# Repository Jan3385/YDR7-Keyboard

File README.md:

# YDR7-Keyboard

A mechanical keyboard build on YD-RP2040 with an OLED display and backlights

Build for **MX** switches

A sligthly modified 96% keyboard layout with 4 extra keys for managing onboard firmware (103 keys total)

## Why is this one special

It's a keyboard with a customisable OLED that helps to manage, and control parts of the firmware like changing backlighting color, showing typing speed and much more

The firmware is also open-source so anyone can customise and add features to their keyboard

## PCB

The keyboard uses a custom PCB with the YD-RP2040 attached to it providing a USB-C connection along with power to the board

The YD-RP2040 is the devboard with a chip running this project. You may be able to use a standard Raspberry PI pico but that was not tested

## Case

The keyboard is comprised out of 3 parts. The panel which holds the switches, a back panel and a front panel

Due to their size its impossible to print an entire piece at once, thats why there are sliced versions in the `CAD/Sliced` folder. You can print them separately and then weld them with a soldering iron together. You should weld the front and the back piece but not the panels as they are held together by the frame anyway

> [!WARNING]
> Due to the size of the keyboard, even the sliced version requires 216 x 139 mm or larger printing plate

## Compiling & flashing firmware

> [!NOTE]
> You should have CMAKE and GCC installed along with Arm embedded GNU Toolchain `arm-none-eabi-gcc`

For compilation run the following commands in the project folder:
Note that the first command may take a while as it is downloading the SDK from git

> cmake -S Firmware -B Firmware/build -G "Ninja"

> cmake --build Firmware/build --target Keyboard_Firmware

To load the firmware into the RP2040 chip, press the **BOOT** button on the YD-RP2040 devboard and plug it into your computer. It should appear as a drive in which you insert the `Keyboard_Firmware.uf2` file inside the `Firmware/build/` folder. The keyboard should reboot itself and load the active firmware

To reflash the board just repeat the steps above

## BOM

| Product name | Product description | Product link | Product unit cost inc. Tax (€) | Product amount | Product total cost (€) | Running total (€ with tax and shipping) |
|---------------|---------------------|---------------|----------------------------------|----------------|------------------------|------------------------------------------|
| YD-RP2040 | RPI pico-like microcontroller board | [Link](https://www.aliexpress.com/item/1005006152339711.html) | 2.99 € | 1 | 2.99 € | 2.99 € |
| 74AHCT125DR | Logic level shifter IO | [Link](https://www.aliexpress.com/item/1005010022053816.html) | 3.01 € | 1 | 3.01 € | 6.00 € |
| 100nF 0805 Ceramic Capacitor (>= 6.3V) | Decoupling capacitor | [Link](https://www.aliexpress.com/item/1005007470747384.html) | 0.02 € | 105 | 1.82 € | 7.82 € |
| 10kΩ 0805 Resistor | Pull-up resistor | [Link](https://www.aliexpress.com/item/1005009805187579.html) | 0.02 € | 2 | 0.04 € | 7.85 € |
| 1N4148W Diode | Keyboard matrix diode | [Link](https://www.aliexpress.com/item/4000685043735.html) | 0.02 € | 103 | 1.77 € | 9.63 € |
| Kailh Hot-Swap Sockets for Gateron x103 | PCB sockets for switches | [Link](https://www.aliexpress.com/item/1005009594313632.html) | 8.24 € | 1 | 8.24 € | 17.87 € |
| Gateron Switch G Pro 3.0 | Mechanical keyboard switches | [Link](https://kurokeeb.com/products/gateron-switch-g-pro-3-0) | 0.37 € | 103 | 38.11 € | 55.98 € |
| 1.5 Inch OLED Display 128x128 I2C | OLED Screen | [Link](https://www.aliexpress.com/item/1005009409829497.html) | 4.25 € | 1 | 4.25 € | 60.23 € |
| SK6812 Mini RGB LED x200 | Backlight LEDs | [Link](https://www.aliexpress.com/item/1005007696173500.html) | 3.38 € | 2 | 6.76 € | 66.99 € |
| Keycap set | set of keycaps for keyboard | [Link](https://www.aliexpress.com/item/1005007996240625.html) | 16.93 € | 1 | 16.93 € | 83.92 € |
| M3x8 screws | screws for PCB and case assembly | [Link](https://www.aliexpress.com/item/1005008585550992.html) | 0.05 € | 8 | 0.40 € | 84.32 € |
| Hot melt inserts MxL4xOD4.2 | inserts for case assembly | [Link](https://www.aliexpress.com/item/1005006071488810.html) | 0.11 € | 8 | 0.88 € | 85.20 € |
| Silicone feet 12x3mm x4 | anti-slip feet for case | [Link](https://www.aliexpress.com/item/1005006954839245.html) | 0.72 € | 1 | 0.72 € | 85.92 € |
| PCB | w/o assembly (estimate) | [Link](https://www.jlcpcb.com/) | 40.00 € | 1 | 40.00 € | 125.92 € |

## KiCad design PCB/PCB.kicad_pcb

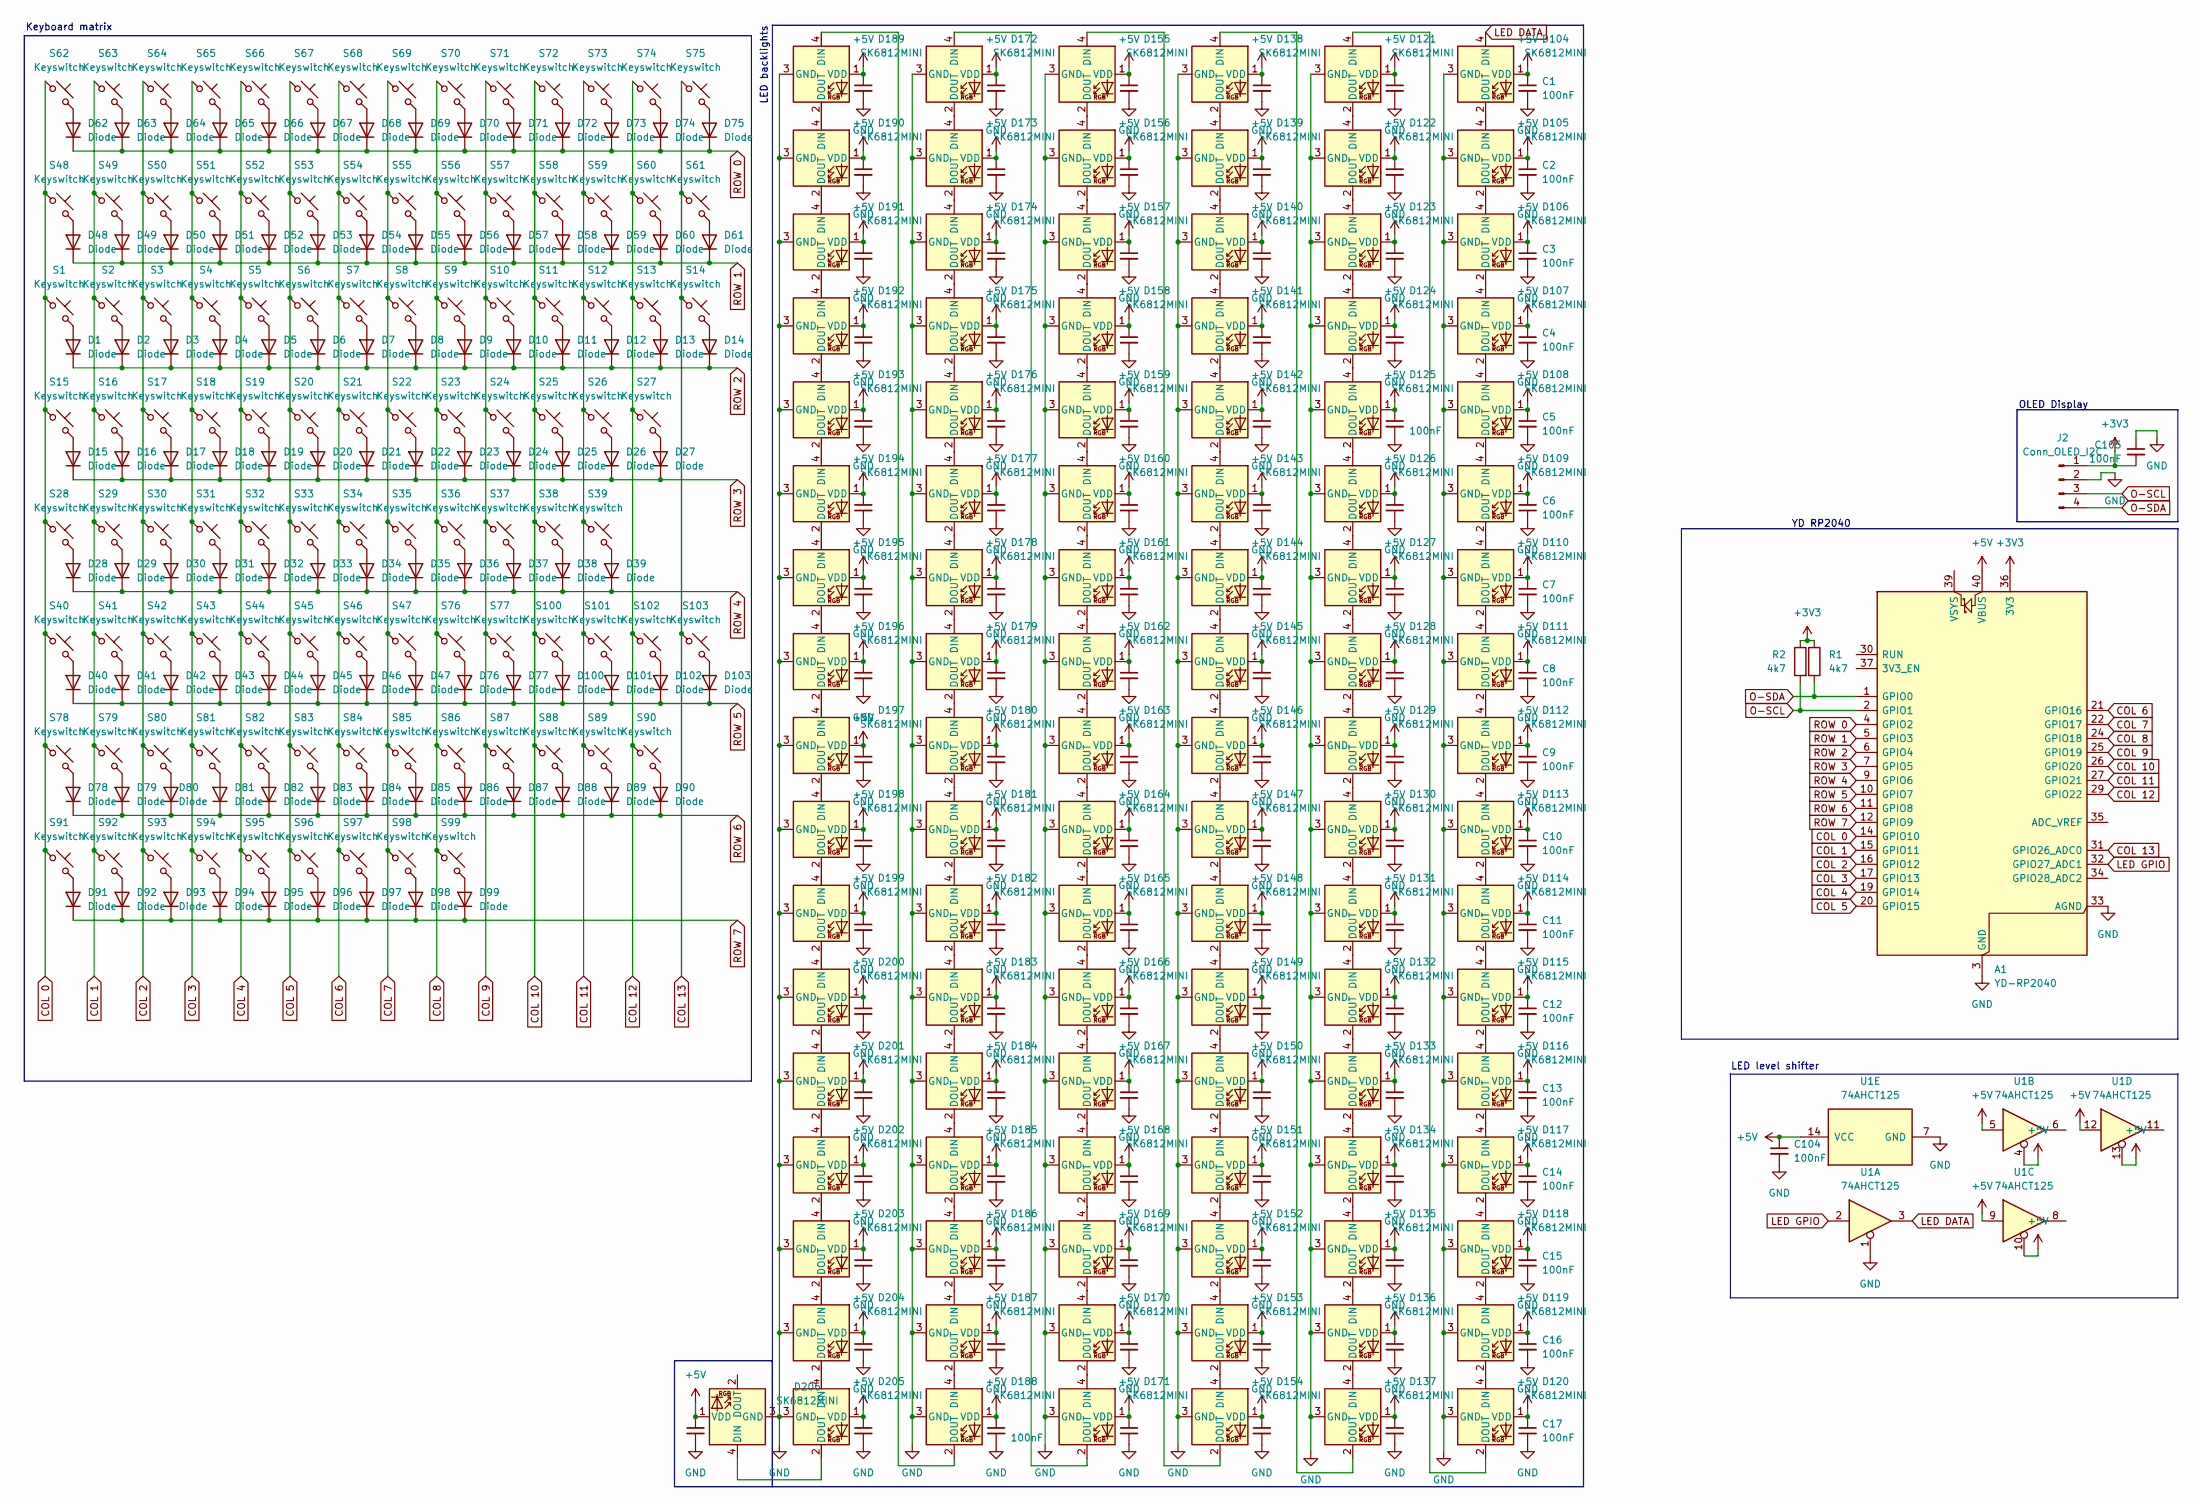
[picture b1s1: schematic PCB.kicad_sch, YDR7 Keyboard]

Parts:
A1: YD-RP2040; RaspberryPi_Pico_SMD_HandSolder
C1, C2, C3, C4, C5, C6, C7, C8, C9, C10, C11, C12, C13, C14, C15, C16, C17, C18, C19, C20, C21, C22, C23, C24, C25, C26, C27, C28, C29, C30, C31, C32, C33, C34, C35, C36, C37, C38, C39, C40, C41, C42, C43, C44, C45, C46, C47, C48, C49, C50, C51, C52, C53, C54, C55, C56, C57, C58, C59, C60, C61, C62, C63, C64, C65, C66, C67, C68, C69, C70, C71, C72, C73, C74, C75, C76, C77, C78, C79, C80, C81, C82, C83, C84, C85, C86, C87, C88, C89, C90, C91, C92, C93, C94, C95, C96, C97, C98, C99, C100, C101, C102, C103, C104, C105: 100nF; C_0805_2012Metric_Pad1.18x1.45mm_HandSolder
D1, D2, D3, D4, D5, D6, D7, D8, D9, D10, D11, D12, D13, D14, D15, D16, D17, D18, D19, D20, D21, D22, D23, D24, D25, D26, D27, D28, D29, D30, D31, D32, D33, D34, D35, D36, D37, D38, D39, D40, D41, D42, D43, D44, D45, D46, D47, D48, D49, D50, D51, D52, D53, D54, D55, D56, D57, D58, D59, D60, D61, D62, D63, D64, D65, D66, D67, D68, D69, D70, D71, D72, D73, D74, D75, D76, D77, D78, D79, D80, D81, D82, D83, D84, D85, D86, D87, D88, D89, D90, D91, D92, D93, D94, D95, D96, D97, D98, D99, D100, D101, D102, D103: Diode; Diode_SOD-123
D104, D105, D106, D107, D108, D109, D110, D111, D112, D113, D114, D115, D116, D117, D118, D119, D120, D121, D122, D123, D124, D125, D126, D127, D128, D129, D130, D131, D132, D133, D134, D135, D136, D137, D138, D139, D140, D141, D142, D143, D144, D145, D146, D147, D148, D149, D150, D151, D152, D153, D154, D155, D156, D157, D158, D159, D160, D161, D162, D163, D164, D165, D166, D167, D168, D169, D170, D171, D172, D173, D174, D175, D176, D177, D178, D179, D180, D181, D182, D183, D184, D185, D186, D187, D188, D189, D190, D191, D192, D193, D194, D195, D196, D197, D198, D199, D200, D201, D202, D203, D204, D205, D206: SK6812MINI; LED_SK6812MINI
J2: Conn_OLED_I2C; PinHeader_1x04_P2.54mm_Vertical
R1, R2: 4k7; R_0805_2012Metric_Pad1.20x1.40mm_HandSolder
S1, S14: Keyswitch; Hotswap_MX_1.50u
S2, S3, S4, S5, S6, S7, S8, S9, S10, S11, S12, S13, S16, S17, S18, S19, S20, S21, S22, S23, S24, S25, S26, S29, S30, S31, S32, S33, S34, S35, S36, S37, S38, S44, S45, S46, S47, S48, S49, S50, S51, S52, S53, S54, S55, S56, S57, S58, S59, S60, S62, S63, S64, S65, S66, S67, S68, S69, S70, S71, S72, S73, S74, S75, S76, S77, S78, S79, S80, S81, S82, S83, S84, S85, S86, S87, S88, S89, S90, S91, S92, S95, S96, S97, S98, S99, S100, S101, S102, S103: Keyswitch; Hotswap_MX_1.00u
S15, S39: Keyswitch; Hotswap_MX_1.75u
S27, S28: Keyswitch; Hotswap_MX_2.25u
S40, S41, S42: Keyswitch; Hotswap_MX_1.25u
S43: Keyswitch; Hotswap_MX_6.25u
S61: Keyswitch; Hotswap_MX_2.00u
S93, S94: Keyswitch; Hotswap_MX_2.00u_90deg
U1: 74AHCT125; SOIC-14_3.9x8.7mm_P1.27mm

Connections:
+3V3: A1.36 (3V3), C105.2, J2.1, R1.1, R2.1
+5V: A1.40 (VBUS), C1.1, C2.1, C3.1, C4.1, C5.1, C6.1, C7.1, C8.1, C9.1, C10.1, C11.1, C12.1, C13.1, C14.1, C15.1, C16.1, C17.1, C18.1, C19.1, C20.1, C21.1, C22.1, C23.1, C24.1, C25.1, C26.1, C27.1, C28.1, C29.1, C30.1, C31.1, C32.1, C33.1, C34.1, C35.1, C36.1, C37.1, C38.1, C39.1, C40.1, C41.1, C42.1, C43.1, C44.1, C45.1, C46.1, C47.1, C48.1, C49.1, C50.1, C51.1, C52.1, C53.1, C54.1, C55.1, C56.1, C57.1, C58.1, C59.1, C60.1, C61.1, C62.1, C63.1, C64.1, C65.1, C66.1, C67.1, C68.1, C69.1, C70.1, C71.1, C72.1, C73.1, C74.1, C75.1, C76.1, C77.1, C78.1, C79.1, C80.1, C81.1, C82.1, C83.1, C84.1, C85.1, C86.1, C87.1, C88.1, C89.1, C90.1, C91.1, C92.1, C93.1, C94.1, C95.1, C96.1, C97.1, C98.1, C99.1, C100.1, C101.1, C102.1, C103.1, C104.1, D104.1 (VDD), D105.1 (VDD), D106.1 (VDD), D107.1 (VDD), D108.1 (VDD), D109.1 (VDD), D110.1 (VDD), D111.1 (VDD), D112.1 (VDD), D113.1 (VDD), D114.1 (VDD), D115.1 (VDD), D116.1 (VDD), D117.1 (VDD), D118.1 (VDD), D119.1 (VDD), D120.1 (VDD), D121.1 (VDD), D122.1 (VDD), D123.1 (VDD), D124.1 (VDD), D125.1 (VDD), D126.1 (VDD), D127.1 (VDD), D128.1 (VDD), D129.1 (VDD), D130.1 (VDD), D131.1 (VDD), D132.1 (VDD), D133.1 (VDD), D134.1 (VDD), D135.1 (VDD), D136.1 (VDD), D137.1 (VDD), D138.1 (VDD), D139.1 (VDD), D140.1 (VDD), D141.1 (VDD), D142.1 (VDD), D143.1 (VDD), D144.1 (VDD), D145.1 (VDD), D146.1 (VDD), D147.1 (VDD), D148.1 (VDD), D149.1 (VDD), D150.1 (VDD), D151.1 (VDD), D152.1 (VDD), D153.1 (VDD), D154.1 (VDD), D155.1 (VDD), D156.1 (VDD), D157.1 (VDD), D158.1 (VDD), D159.1 (VDD), D160.1 (VDD), D161.1 (VDD), D162.1 (VDD), D163.1 (VDD), D164.1 (VDD), D165.1 (VDD), D166.1 (VDD), D167.1 (VDD), D168.1 (VDD), D169.1 (VDD), D170.1 (VDD), D171.1 (VDD), D172.1 (VDD), D173.1 (VDD), D174.1 (VDD), D175.1 (VDD), D176.1 (VDD), D177.1 (VDD), D178.1 (VDD), D179.1 (VDD), D180.1 (VDD), D181.1 (VDD), D182.1 (VDD), D183.1 (VDD), D184.1 (VDD), D185.1 (VDD), D186.1 (VDD), D187.1 (VDD), D188.1 (VDD), D189.1 (VDD), D190.1 (VDD), D191.1 (VDD), D192.1 (VDD), D193.1 (VDD), D194.1 (VDD), D195.1 (VDD), D196.1 (VDD), D197.1 (VDD), D198.1 (VDD), D199.1 (VDD), D200.1 (VDD), D201.1 (VDD), D202.1 (VDD), D203.1 (VDD), D204.1 (VDD), D205.1 (VDD), D206.1 (VDD), U1.4, U1.5, U1.9, U1.10, U1.12, U1.13, U1.14 (VCC)
COL 0: A1.14 (GPIO10), S1.1, S15.1, S28.1, S40.1, S48.1, S62.1, S78.1, S91.1
COL 1: A1.15 (GPIO11), S2.1, S16.1, S29.1, S41.1, S49.1, S63.1, S79.1, S92.1
COL 2: A1.16 (GPIO12), S3.1, S17.1, S30.1, S42.1, S50.1, S64.1, S80.1, S93.1
COL 3: A1.17 (GPIO13), S4.1, S18.1, S31.1, S43.1, S51.1, S65.1, S81.1, S94.1
COL 4: A1.19 (GPIO14), S5.1, S19.1, S32.1, S44.1, S52.1, S66.1, S82.1, S95.1
COL 5: A1.20 (GPIO15), S6.1, S20.1, S33.1, S45.1, S53.1, S67.1, S83.1, S96.1
COL 6: A1.21 (GPIO16), S7.1, S21.1, S34.1, S46.1, S54.1, S68.1, S84.1, S97.1
COL 7: A1.22 (GPIO17), S8.1, S22.1, S35.1, S47.1, S55.1, S69.1, S85.1, S98.1
COL 8: A1.24 (GPIO18), S9.1, S23.1, S36.1, S56.1, S70.1, S76.1, S86.1, S99.1
COL 9: A1.25 (GPIO19), S10.1, S24.1, S37.1, S57.1, S71.1, S77.1, S87.1
COL 10: A1.26 (GPIO20), S11.1, S25.1, S38.1, S58.1, S72.1, S88.1, S100.1
COL 11: A1.27 (GPIO21), S12.1, S26.1, S39.1, S59.1, S73.1, S89.1, S101.1
COL 12: A1.29 (GPIO22), S13.1, S27.1, S60.1, S74.1, S90.1, S102.1
COL 13: A1.31 (GPIO26_ADC0), S14.1, S61.1, S75.1, S103.1
GND: A1.3 (GND), A1.8 (GND), A1.13 (GND), A1.18 (GND), A1.23 (GND), A1.28 (GND), A1.33 (AGND), A1.38 (GND), C1.2, C2.2, C3.2, C4.2, C5.2, C6.2, C7.2, C8.2, C9.2, C10.2, C11.2, C12.2, C13.2, C14.2, C15.2, C16.2, C17.2, C18.2, C19.2, C20.2, C21.2, C22.2, C23.2, C24.2, C25.2, C26.2, C27.2, C28.2, C29.2, C30.2, C31.2, C32.2, C33.2, C34.2, C35.2, C36.2, C37.2, C38.2, C39.2, C40.2, C41.2, C42.2, C43.2, C44.2, C45.2, C46.2, C47.2, C48.2, C49.2, C50.2, C51.2, C52.2, C53.2, C54.2, C55.2, C56.2, C57.2, C58.2, C59.2, C60.2, C61.2, C62.2, C63.2, C64.2, C65.2, C66.2, C67.2, C68.2, C69.2, C70.2, C71.2, C72.2, C73.2, C74.2, C75.2, C76.2, C77.2, C78.2, C79.2, C80.2, C81.2, C82.2, C83.2, C84.2, C85.2, C86.2, C87.2, C88.2, C89.2, C90.2, C91.2, C92.2, C93.2, C94.2, C95.2, C96.2, C97.2, C98.2, C99.2, C100.2, C101.2, C102.2, C103.2, C104.2, C105.1, D104.3 (GND), D105.3 (GND), D106.3 (GND), D107.3 (GND), D108.3 (GND), D109.3 (GND), D110.3 (GND), D111.3 (GND), D112.3 (GND), D113.3 (GND), D114.3 (GND), D115.3 (GND), D116.3 (GND), D117.3 (GND), D118.3 (GND), D119.3 (GND), D120.3 (GND), D121.3 (GND), D122.3 (GND), D123.3 (GND), D124.3 (GND), D125.3 (GND), D126.3 (GND), D127.3 (GND), D128.3 (GND), D129.3 (GND), D130.3 (GND), D131.3 (GND), D132.3 (GND), D133.3 (GND), D134.3 (GND), D135.3 (GND), D136.3 (GND), D137.3 (GND), D138.3 (GND), D139.3 (GND), D140.3 (GND), D141.3 (GND), D142.3 (GND), D143.3 (GND), D144.3 (GND), D145.3 (GND), D146.3 (GND), D147.3 (GND), D148.3 (GND), D149.3 (GND), D150.3 (GND), D151.3 (GND), D152.3 (GND), D153.3 (GND), D154.3 (GND), D155.3 (GND), D156.3 (GND), D157.3 (GND), D158.3 (GND), D159.3 (GND), D160.3 (GND), D161.3 (GND), D162.3 (GND), D163.3 (GND), D164.3 (GND), D165.3 (GND), D166.3 (GND), D167.3 (GND), D168.3 (GND), D169.3 (GND), D170.3 (GND), D171.3 (GND), D172.3 (GND), D173.3 (GND), D174.3 (GND), D175.3 (GND), D176.3 (GND), D177.3 (GND), D178.3 (GND), D179.3 (GND), D180.3 (GND), D181.3 (GND), D182.3 (GND), D183.3 (GND), D184.3 (GND), D185.3 (GND), D186.3 (GND), D187.3 (GND), D188.3 (GND), D189.3 (GND), D190.3 (GND), D191.3 (GND), D192.3 (GND), D193.3 (GND), D194.3 (GND), D195.3 (GND), D196.3 (GND), D197.3 (GND), D198.3 (GND), D199.3 (GND), D200.3 (GND), D201.3 (GND), D202.3 (GND), D203.3 (GND), D204.3 (GND), D205.3 (GND), D206.3 (GND), J2.2, U1.1, U1.7 (GND)
LED DATA: D104.4 (DIN), U1.3
LED GPIO: A1.32 (GPIO27_ADC1), U1.2
unnamed: D1.2 (A), S1.2
unnamed: D2.2 (A), S2.2
unnamed: D3.2 (A), S3.2
unnamed: D4.2 (A), S4.2
unnamed: D5.2 (A), S5.2
unnamed: D6.2 (A), S6.2
unnamed: D7.2 (A), S7.2
unnamed: D8.2 (A), S8.2
unnamed: D9.2 (A), S9.2
unnamed: D10.2 (A), S10.2
unnamed: D11.2 (A), S11.2
unnamed: D12.2 (A), S12.2
unnamed: D13.2 (A), S13.2
unnamed: D14.2 (A), S14.2
unnamed: D15.2 (A), S15.2
unnamed: D16.2 (A), S16.2
unnamed: D17.2 (A), S17.2
unnamed: D18.2 (A), S18.2
unnamed: D19.2 (A), S19.2
unnamed: D20.2 (A), S20.2
unnamed: D21.2 (A), S21.2
unnamed: D22.2 (A), S22.2
unnamed: D23.2 (A), S23.2
unnamed: D24.2 (A), S24.2
unnamed: D25.2 (A), S25.2
unnamed: D26.2 (A), S26.2
unnamed: D27.2 (A), S27.2
unnamed: D28.2 (A), S28.2
unnamed: D29.2 (A), S29.2
unnamed: D30.2 (A), S30.2
unnamed: D31.2 (A), S31.2
unnamed: D32.2 (A), S32.2
unnamed: D33.2 (A), S33.2
unnamed: D34.2 (A), S34.2
unnamed: D35.2 (A), S35.2
unnamed: D36.2 (A), S36.2
unnamed: D37.2 (A), S37.2
unnamed: D38.2 (A), S38.2
unnamed: D39.2 (A), S39.2
unnamed: D40.2 (A), S40.2
unnamed: D41.2 (A), S41.2
unnamed: D42.2 (A), S42.2
unnamed: D43.2 (A), S43.2
unnamed: D44.2 (A), S44.2
unnamed: D45.2 (A), S45.2
unnamed: D46.2 (A), S46.2
unnamed: D47.2 (A), S47.2
unnamed: D48.2 (A), S48.2
unnamed: D49.2 (A), S49.2
unnamed: D50.2 (A), S50.2
unnamed: D51.2 (A), S51.2
unnamed: D52.2 (A), S52.2
unnamed: D53.2 (A), S53.2
unnamed: D54.2 (A), S54.2
unnamed: D55.2 (A), S55.2
unnamed: D56.2 (A), S56.2
unnamed: D57.2 (A), S57.2
unnamed: D58.2 (A), S58.2
unnamed: D59.2 (A), S59.2
unnamed: D60.2 (A), S60.2
unnamed: D61.2 (A), S61.2
unnamed: D62.2 (A), S62.2
unnamed: D63.2 (A), S63.2
unnamed: D64.2 (A), S64.2
unnamed: D65.2 (A), S65.2
unnamed: D66.2 (A), S66.2
unnamed: D67.2 (A), S67.2
unnamed: D68.2 (A), S68.2
unnamed: D69.2 (A), S69.2
unnamed: D70.2 (A), S70.2
unnamed: D71.2 (A), S71.2
unnamed: D72.2 (A), S72.2
unnamed: D73.2 (A), S73.2
unnamed: D74.2 (A), S74.2
unnamed: D75.2 (A), S75.2
unnamed: D76.2 (A), S76.2
unnamed: D77.2 (A), S77.2
unnamed: D78.2 (A), S78.2
unnamed: D79.2 (A), S79.2
unnamed: D80.2 (A), S80.2
unnamed: D81.2 (A), S81.2
unnamed: D82.2 (A), S82.2
unnamed: D83.2 (A), S83.2
unnamed: D84.2 (A), S84.2
unnamed: D85.2 (A), S85.2
unnamed: D86.2 (A), S86.2
unnamed: D87.2 (A), S87.2
unnamed: D88.2 (A), S88.2
unnamed: D89.2 (A), S89.2
unnamed: D90.2 (A), S90.2
unnamed: D91.2 (A), S91.2
unnamed: D92.2 (A), S92.2
unnamed: D93.2 (A), S93.2
unnamed: D94.2 (A), S94.2
unnamed: D95.2 (A), S95.2
unnamed: D96.2 (A), S96.2
unnamed: D97.2 (A), S97.2
unnamed: D98.2 (A), S98.2
unnamed: D99.2 (A), S99.2
unnamed: D100.2 (A), S100.2
unnamed: D101.2 (A), S101.2
unnamed: D102.2 (A), S102.2
unnamed: D103.2 (A), S103.2
unnamed: D104.2 (DOUT), D105.4 (DIN)
unnamed: D105.2 (DOUT), D106.4 (DIN)
unnamed: D106.2 (DOUT), D107.4 (DIN)
unnamed: D107.2 (DOUT), D108.4 (DIN)
unnamed: D108.2 (DOUT), D109.4 (DIN)
unnamed: D109.2 (DOUT), D110.4 (DIN)
unnamed: D110.2 (DOUT), D111.4 (DIN)
unnamed: D111.2 (DOUT), D112.4 (DIN)
unnamed: D112.2 (DOUT), D113.4 (DIN)
unnamed: D113.2 (DOUT), D114.4 (DIN)
unnamed: D114.2 (DOUT), D115.4 (DIN)
unnamed: D115.2 (DOUT), D116.4 (DIN)
unnamed: D116.2 (DOUT), D117.4 (DIN)
unnamed: D117.2 (DOUT), D118.4 (DIN)
unnamed: D118.2 (DOUT), D119.4 (DIN)
unnamed: D119.2 (DOUT), D120.4 (DIN)
unnamed: D120.2 (DOUT), D121.4 (DIN)
unnamed: D121.2 (DOUT), D122.4 (DIN)
unnamed: D122.2 (DOUT), D123.4 (DIN)
unnamed: D123.2 (DOUT), D124.4 (DIN)
unnamed: D124.2 (DOUT), D125.4 (DIN)
unnamed: D125.2 (DOUT), D126.4 (DIN)
unnamed: D126.2 (DOUT), D127.4 (DIN)
unnamed: D127.2 (DOUT), D128.4 (DIN)
unnamed: D128.2 (DOUT), D129.4 (DIN)
unnamed: D129.2 (DOUT), D130.4 (DIN)
unnamed: D130.2 (DOUT), D131.4 (DIN)
unnamed: D131.2 (DOUT), D132.4 (DIN)
unnamed: D132.2 (DOUT), D133.4 (DIN)
unnamed: D133.2 (DOUT), D134.4 (DIN)
unnamed: D134.2 (DOUT), D135.4 (DIN)
unnamed: D135.2 (DOUT), D136.4 (DIN)
unnamed: D136.2 (DOUT), D137.4 (DIN)
unnamed: D137.2 (DOUT), D138.4 (DIN)
unnamed: D138.2 (DOUT), D139.4 (DIN)
unnamed: D139.2 (DOUT), D140.4 (DIN)
unnamed: D140.2 (DOUT), D141.4 (DIN)
unnamed: D141.2 (DOUT), D142.4 (DIN)
unnamed: D142.2 (DOUT), D143.4 (DIN)
unnamed: D143.2 (DOUT), D144.4 (DIN)
unnamed: D144.2 (DOUT), D145.4 (DIN)
unnamed: D145.2 (DOUT), D146.4 (DIN)
unnamed: D146.2 (DOUT), D147.4 (DIN)
unnamed: D147.2 (DOUT), D148.4 (DIN)
unnamed: D148.2 (DOUT), D149.4 (DIN)
unnamed: D149.2 (DOUT), D150.4 (DIN)
unnamed: D150.2 (DOUT), D151.4 (DIN)
unnamed: D151.2 (DOUT), D152.4 (DIN)
unnamed: D152.2 (DOUT), D153.4 (DIN)
unnamed: D153.2 (DOUT), D154.4 (DIN)
unnamed: D154.2 (DOUT), D155.4 (DIN)
unnamed: D155.2 (DOUT), D156.4 (DIN)
unnamed: D156.2 (DOUT), D157.4 (DIN)
unnamed: D157.2 (DOUT), D158.4 (DIN)
unnamed: D158.2 (DOUT), D159.4 (DIN)
unnamed: D159.2 (DOUT), D160.4 (DIN)
unnamed: D160.2 (DOUT), D161.4 (DIN)
unnamed: D161.2 (DOUT), D162.4 (DIN)
unnamed: D162.2 (DOUT), D163.4 (DIN)
unnamed: D163.2 (DOUT), D164.4 (DIN)
unnamed: D164.2 (DOUT), D165.4 (DIN)
unnamed: D165.2 (DOUT), D166.4 (DIN)
unnamed: D166.2 (DOUT), D167.4 (DIN)
unnamed: D167.2 (DOUT), D168.4 (DIN)
unnamed: D168.2 (DOUT), D169.4 (DIN)
unnamed: D169.2 (DOUT), D170.4 (DIN)
unnamed: D170.2 (DOUT), D171.4 (DIN)
unnamed: D171.2 (DOUT), D172.4 (DIN)
unnamed: D172.2 (DOUT), D173.4 (DIN)
unnamed: D173.2 (DOUT), D174.4 (DIN)
unnamed: D174.2 (DOUT), D175.4 (DIN)
unnamed: D175.2 (DOUT), D176.4 (DIN)
unnamed: D176.2 (DOUT), D177.4 (DIN)
unnamed: D177.2 (DOUT), D178.4 (DIN)
unnamed: D178.2 (DOUT), D179.4 (DIN)
unnamed: D179.2 (DOUT), D180.4 (DIN)
unnamed: D180.2 (DOUT), D181.4 (DIN)
unnamed: D181.2 (DOUT), D182.4 (DIN)
unnamed: D182.2 (DOUT), D183.4 (DIN)
unnamed: D183.2 (DOUT), D184.4 (DIN)
unnamed: D184.2 (DOUT), D185.4 (DIN)
unnamed: D185.2 (DOUT), D186.4 (DIN)
unnamed: D186.2 (DOUT), D187.4 (DIN)
unnamed: D187.2 (DOUT), D188.4 (DIN)
unnamed: D188.2 (DOUT), D189.4 (DIN)
unnamed: D189.2 (DOUT), D190.4 (DIN)
unnamed: D190.2 (DOUT), D191.4 (DIN)
unnamed: D191.2 (DOUT), D192.4 (DIN)
unnamed: D192.2 (DOUT), D193.4 (DIN)
unnamed: D193.2 (DOUT), D194.4 (DIN)
unnamed: D194.2 (DOUT), D195.4 (DIN)
unnamed: D195.2 (DOUT), D196.4 (DIN)
unnamed: D196.2 (DOUT), D197.4 (DIN)
unnamed: D197.2 (DOUT), D198.4 (DIN)
unnamed: D198.2 (DOUT), D199.4 (DIN)
unnamed: D199.2 (DOUT), D200.4 (DIN)
unnamed: D200.2 (DOUT), D201.4 (DIN)
unnamed: D201.2 (DOUT), D202.4 (DIN)
unnamed: D202.2 (DOUT), D203.4 (DIN)
unnamed: D203.2 (DOUT), D204.4 (DIN)
unnamed: D204.2 (DOUT), D205.4 (DIN)
unnamed: D205.2 (DOUT), D206.4 (DIN)
O-SCL: A1.2 (GPIO1), J2.3, R2.2
O-SDA: A1.1 (GPIO0), J2.4, R1.2
ROW 0: A1.4 (GPIO2), D62.1 (K), D63.1 (K), D64.1 (K), D65.1 (K), D66.1 (K), D67.1 (K), D68.1 (K), D69.1 (K), D70.1 (K), D71.1 (K), D72.1 (K), D73.1 (K), D74.1 (K), D75.1 (K)
ROW 1: A1.5 (GPIO3), D48.1 (K), D49.1 (K), D50.1 (K), D51.1 (K), D52.1 (K), D53.1 (K), D54.1 (K), D55.1 (K), D56.1 (K), D57.1 (K), D58.1 (K), D59.1 (K), D60.1 (K), D61.1 (K)
ROW 2: A1.6 (GPIO4), D1.1 (K), D2.1 (K), D3.1 (K), D4.1 (K), D5.1 (K), D6.1 (K), D7.1 (K), D8.1 (K), D9.1 (K), D10.1 (K), D11.1 (K), D12.1 (K), D13.1 (K), D14.1 (K)
ROW 3: A1.7 (GPIO5), D15.1 (K), D16.1 (K), D17.1 (K), D18.1 (K), D19.1 (K), D20.1 (K), D21.1 (K), D22.1 (K), D23.1 (K), D24.1 (K), D25.1 (K), D26.1 (K), D27.1 (K)
ROW 4: A1.9 (GPIO6), D28.1 (K), D29.1 (K), D30.1 (K), D31.1 (K), D32.1 (K), D33.1 (K), D34.1 (K), D35.1 (K), D36.1 (K), D37.1 (K), D38.1 (K), D39.1 (K)
ROW 5: A1.10 (GPIO7), D40.1 (K), D41.1 (K), D42.1 (K), D43.1 (K), D44.1 (K), D45.1 (K), D46.1 (K), D47.1 (K), D76.1 (K), D77.1 (K), D100.1 (K), D101.1 (K), D102.1 (K), D103.1 (K)
ROW 6: A1.11 (GPIO8), D78.1 (K), D79.1 (K), D80.1 (K), D81.1 (K), D82.1 (K), D83.1 (K), D84.1 (K), D85.1 (K), D86.1 (K), D87.1 (K), D88.1 (K), D89.1 (K), D90.1 (K)
ROW 7: A1.12 (GPIO9), D91.1 (K), D92.1 (K), D93.1 (K), D94.1 (K), D95.1 (K), D96.1 (K), D97.1 (K), D98.1 (K), D99.1 (K)

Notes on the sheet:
LED backlights
Keyboard matrix
OLED Display
YD RP2040
LED level shifter

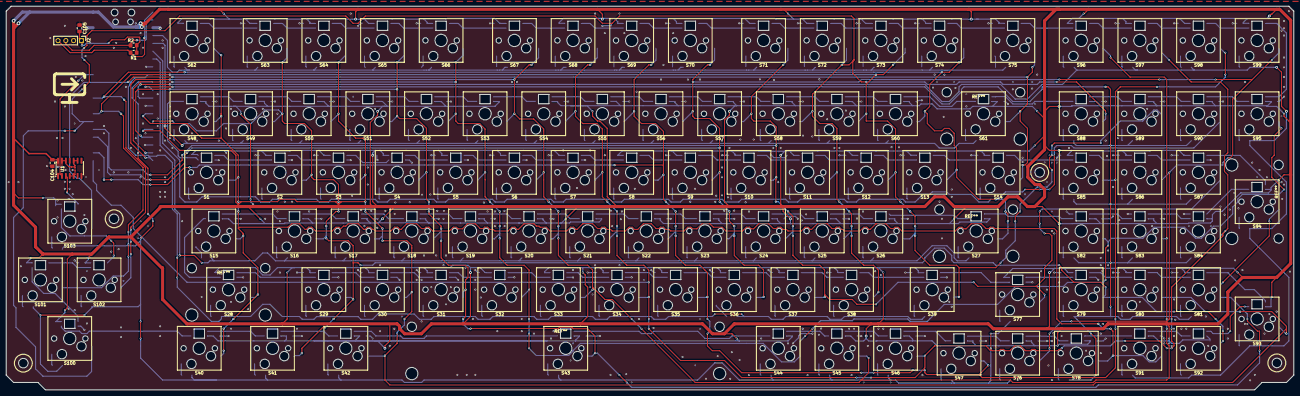
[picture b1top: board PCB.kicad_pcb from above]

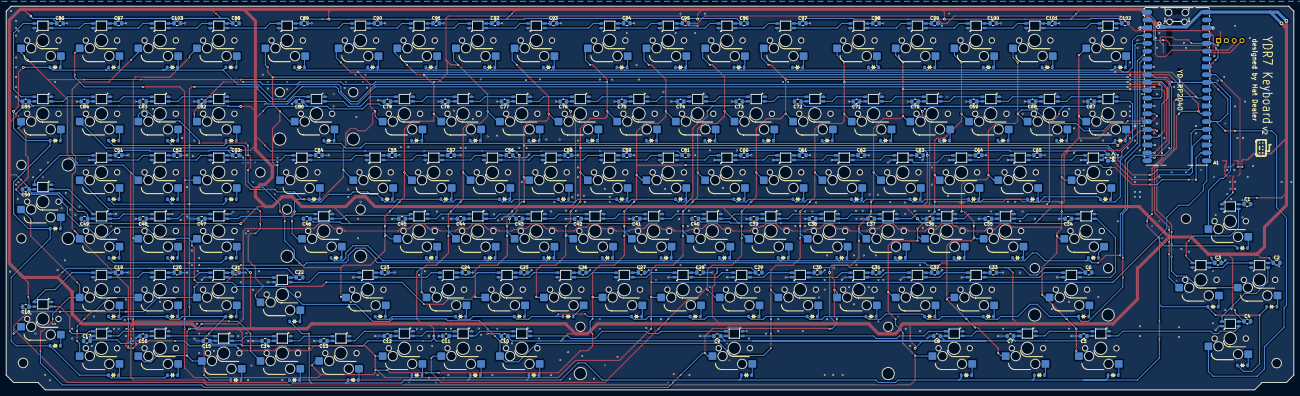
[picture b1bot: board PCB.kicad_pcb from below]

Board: 2 copper layers, 418.3 x 124.6 mm, 419 parts (310 on the bottom side), 234 nets.

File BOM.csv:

Product name,Product description,Product link,Product unit cost inc. Tax (€),Product amount,Product total cost (€),Running total (€ with tax and shipping)
YD-RP2040,RPI pico-like microcontroller board,https://www.aliexpress.com/item/1005006152339711.html, 2.99 € ,1, 2.99 € , 2.99 € 
74AHCT125DR,Logic level shifter IO,https://www.aliexpress.com/item/1005010022053816.html, 3.01 € ,1, 3.01 € , 6.00 € 
100nF 0805 Ceramic Capacitor (>= 6.3V),Decoupling capacitor,https://www.aliexpress.com/item/1005007470747384.html, 0.02 € ,105, 1.82 € , 7.82 € 
10kΩ 0805 Resistor,Pull-up resistor,https://www.aliexpress.com/item/1005009805187579.html, 0.02 € ,2, 0.04 € , 7.85 € 
1N4148W Diode,Keyboard matrix diode,https://www.aliexpress.com/item/4000685043735.html, 0.02 € ,103, 1.77 € , 9.63 € 
Kailh Hot-Swap Sockets for Gateron x103,PCB sockets for switches,https://www.aliexpress.com/item/1005009594313632.html, 8.24 € ,1, 8.24 € , 17.87 € 
Gateron Switch G Pro 3.0,Mechanical keyboard switches,https://kurokeeb.com/products/gateron-switch-g-pro-3-0, 0.37 € ,103, 38.11 € , 55.98 € 
1.5 Inch OLED Display 128x128 I2C,OLED Screen,https://www.aliexpress.com/item/1005009409829497.html, 4.25 € ,1, 4.25 € , 60.23 € 
SK6812 Mini RGB LED x200,Backlight LEDs,https://www.aliexpress.com/item/1005007696173500.html, 3.38 € ,2, 6.76 € , 66.99 € 
Keycap set,set of keycaps for keyboard,https://www.aliexpress.com/item/1005007996240625.html, 16.93 € ,1, 16.93 € , 83.92 € 
M3x8 screws,screws for PCB and case assembly,https://www.aliexpress.com/item/1005008585550992.html, 0.05 € ,8, 0.40 € , 84.32 € 
Hot melt inserts MxL4xOD4.2,inserts for case assembly,https://www.aliexpress.com/item/1005006071488810.html, 0.11 € ,8, 0.88 € , 85.20 € 
Silicone feet 12x3mm x4,anti-slip feet for case,https://www.aliexpress.com/item/1005006954839245.html, 0.72 € ,1, 0.72 € , 85.92 € 
PCB,w/o assembly (estimate),https://www.jlcpcb.com/, 40.00 € ,1, 40.00 € , 125.92 €

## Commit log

2025-10-28 made a really small readme
2025-10-29 Schematic with uncomplete PCB
2025-10-29 minor schematic change
2025-10-30 flipped condensators
2025-10-31 did most of the wiring
2025-11-01 wiring is now without errors
2025-11-01 small changes to the PCB
2025-11-01 basic firmware setup
2025-11-01 made basic firmware that just spams "A" as a keyboard
2025-11-01 made firmware timing better
2025-11-01 added BOM
2025-11-01 cosmetic changes to the PCB
2025-11-01 fixed firmware and changet the PCB a little
2025-11-02 added decoupling capacitor near level shifter
2025-11-02 added some vias to lower LEDs signal impedance
2025-11-02 made the PCB not rectangle and updated BOM
2025-11-02 moved some vias around
2025-11-04 wip CAD files
2025-11-05 small readme update
2025-11-05 CAD models for keyboard casing
2025-11-05 stl, readme and bom updates
2025-11-05 addes sliced CAD files
2025-11-05 added a warning
2025-11-05 fixed readme warning and note
2025-11-05 minor changes to readme
2025-11-05 Added filament to the BOM
2025-11-05 updated the PCB a little bit
2025-11-06 updated BOM
2025-11-06 mini BOM update
2025-11-06 Updated BOM to add shiping costs
2025-11-06 updated shipping in the readme too
2025-11-07 Updated BOM, Assembly etc
2025-11-07 updated gerber files
2025-11-07 fixed a wierd typo
2025-11-08 fixed a layout error and updated the assembly with switches
2025-11-19 updated CAD files & PCB
2025-12-02 updated the case
2025-12-03 basic firmware update
2025-12-08 remade the NeoPixels on the PCB
2025-12-08 Added extra routes for the NeoPixels to even out power distribution
2025-12-10 Updated the PCB a bit
2025-12-10 mini update to YD-RP2040 footprint
2025-12-10 updated screw holes on the PCB
2025-12-23 Added basic keyboard functionality + minor CAD change
2025-12-23 minor upgrades
2025-12-23 fixed errors that showed up in my IDE
2025-12-23 changed up the LED colors
2025-12-23 file update + firmware LED control
2025-12-23 added a mini boot sequence
2025-12-23 extra message on boot
2025-12-26 made some functions private, added better gb cap
2025-12-27 added a very basic menu
2025-12-27 Made data transfer multithreaded to make typing more reliable
2025-12-28 separated menu with display logic
2025-12-28 Capslock and numlock now glow when toggled
2026-01-02 gitignore update
2026-01-07 added themes to neopixel colors
